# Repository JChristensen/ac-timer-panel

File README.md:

# Switch and LED PCB for AC timer project  
https://github.com/JChristensen/ac-timer-panel  
README file  
Jack Christensen  
Jul-2023

## License
  
This work is licensed under the [Creative Commons Attribution-ShareAlike 4.0 International License](https://creativecommons.org/licenses/by-sa/4.0/).

## See also
https://github.com/JChristensen/ac-timer-hw

## Assembly tips
1. Solder the switch and headers to the board.
2. Fit the LEDs to the front panel/box lid.
3. Fit the board to the panel, inserting the LED leads.
4. Tighten the nut on the pushbutton switch.
5. Solder and trim the LED leads. Note you have to work under the headers to solder the one LED.

## Drill guide

## Sample assembly

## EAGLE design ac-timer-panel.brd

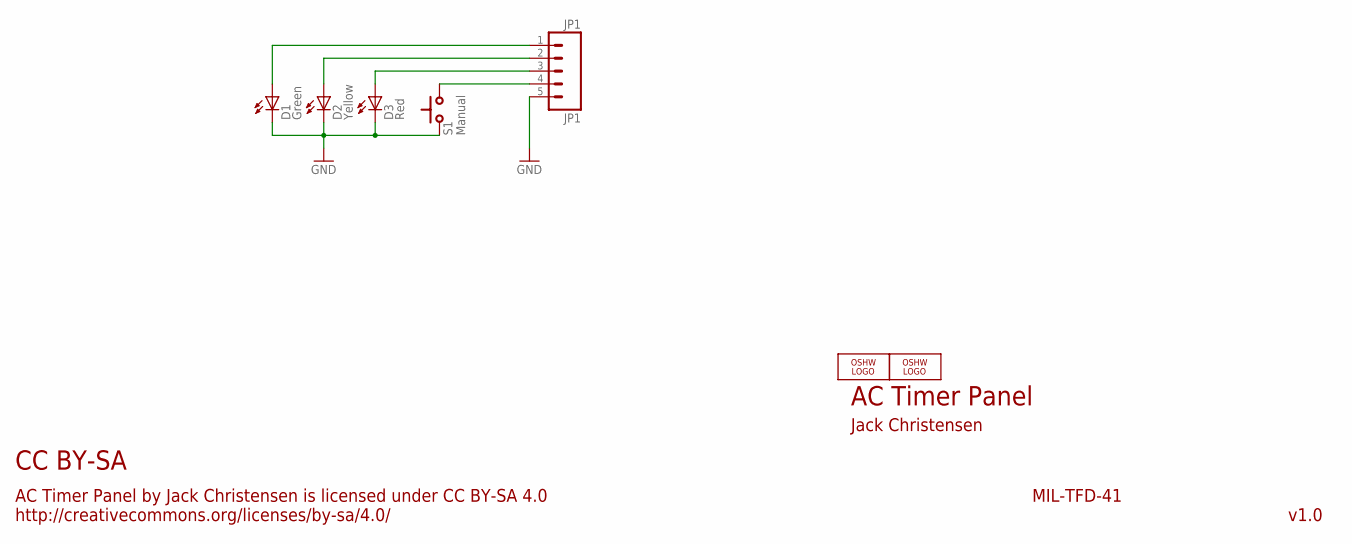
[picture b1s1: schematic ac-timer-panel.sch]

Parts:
D1: Green; LED5MM-OVAL
D2: Yellow; LED5MM-OVAL
D3: Red; LED5MM-OVAL
JP1: JP1; 1X05_LOCK
LOGO1, LOGO2: OSHW_LOGO_8MILX0100-NT; OSHW_8X100_NOTEXT
S1: Manual; SPST-NO-MC

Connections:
GND: D1.K (C), D2.K (C), D3.K (C), JP1.5, S1.P$2
unnamed: D3.A, JP1.3
unnamed: D2.A, JP1.2
unnamed: D1.A, JP1.1
unnamed: JP1.4, S1.P$1

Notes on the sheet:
AC Timer Panel
Jack Christensen
AC Timer Panel by Jack Christensen is licensed under CC BY-SA 4.0 http://creativecommons.org/licenses/by-sa/4.0/
CC BY-SA
v1.0
MIL-TFD-41

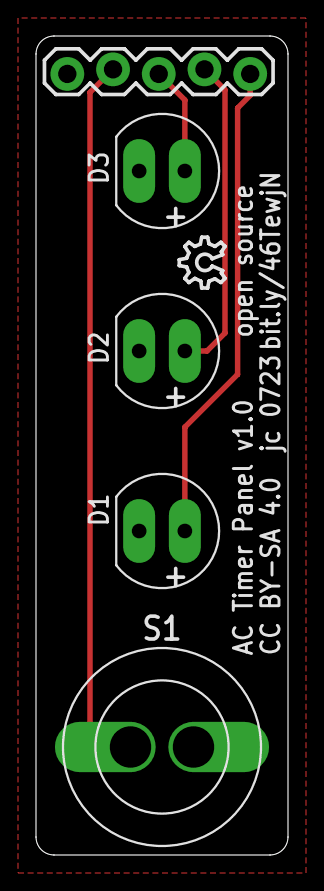
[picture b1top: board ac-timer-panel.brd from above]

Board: 2 copper layers, 14.0 x 45.5 mm, 7 parts (1 on the bottom side), 5 nets.

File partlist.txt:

Partlist

Exported from ac-timer-panel.sch at 7/19/23 8:09 PM

EAGLE Version 9.6.2 Copyright (c) 1988-2020 Autodesk, Inc.

Assembly variant: 

Part     Value          Device               Package     Library  Sheet

D1       Green          LED5MM-LONGPADS      LED5MM-OVAL _jc      1
D2       Yellow         LED5MM-LONGPADS      LED5MM-OVAL _jc      1
D3       Red            LED5MM-LONGPADS      LED5MM-OVAL _jc      1
JP1      JP1            M05LOCK              1X05_LOCK   SparkFun 1
S1       Manual         SPST-NO-MCPUSHBUTTON SPST-NO-MC  _jc      1

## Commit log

2023-07-20 Initial commit.
2023-08-07 Add README and photos.
2023-08-07 Add LICENSE.txt file.

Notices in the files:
ac-timer-panel.brd:
CC BY-SA 4.0  jc 0723
parts and their libraries:
SparkFun: Licensing: CC v3.0 Share-Alike You are welcome to use this library for commercial purposes.
